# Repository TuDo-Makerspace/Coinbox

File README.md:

# Coinbox <!-- omit in toc -->

Our sacred Mario-themed coinbox!

https://github.com/user-attachments/assets/13c91ebd-0a8e-42fc-bb54-711a1d9b547c

## Table of Contents <!-- omit in toc -->

- [Building the Box](#building-the-box)
  - [Step 1. Cut the Wood](#step-1-cut-the-wood)
  - [Step 2. Glue the Pieces Together](#step-2-glue-the-pieces-together)
  - [Step 3. Secure the Bottom](#step-3-secure-the-bottom)
  - [Step 4. Lid slit](#step-4-lid-slit)
  - [Step 5. Hole for DC Jack](#step-5-hole-for-dc-jack)
  - [Step 6. Paint the Base Coat](#step-6-paint-the-base-coat)
  - [Step 7. Draw the Pixel Grid](#step-7-draw-the-pixel-grid)
  - [Step 8. Paint the Pixel Art](#step-8-paint-the-pixel-art)
  - [Step 9. Magnets for the Lid](#step-9-magnets-for-the-lid)
- [Electronics](#electronics)
  - [Components Required](#components-required)
  - [Wiring the Components](#wiring-the-components)
- [Software](#software)
  - [Overview](#overview)
  - [Configurable Parameters](#configurable-parameters)
  - [Sound Playback Implementation](#sound-playback-implementation)
- [Flashing the Arduino](#flashing-the-arduino)
- [Electronics Enclosure](#electronics-enclosure)
  - [Enclosure Components](#enclosure-components)
  - [Assembly Instructions](#assembly-instructions)
    - [1. Mounting the Perfboard](#1-mounting-the-perfboard)
    - [2. Attaching Speaker and Sensor](#2-attaching-speaker-and-sensor)
    - [3. Connecting Components](#3-connecting-components)
    - [4. Securing the Enclosure](#4-securing-the-enclosure)
    - [5. Sensor Calibration](#5-sensor-calibration)
    - [6. Screwing on the Lid](#6-screwing-on-the-lid)

## Building the Box

### Step 1. Cut the Wood

For the box, we cut 2 slightly larger pieces (dimensions: X x Y x Z) and 4 slightly smaller pieces (dimensions: X x Y x Z). The larger pieces make up the top and bottom, while the smaller pieces form the sides.

<div align="center">
  
</div>

### Step 2. Glue the Pieces Together

Once the pieces are cut, glue them together to form the box. Make sure the edges are flush and the corners are square.

<div align="center">
  
</div>

### Step 3. Secure the Bottom

Attach the bottom of the box using screws or nails for extra stability. Glue alone can work but might not be as durable.

<div align="center">
  
</div>

### Step 4. Lid slit

Cut a slit in the lid to allow coins to be inserted into the box. Make sure the slit is wide enough to accommodate different coin sizes.
We used a size of X x Y.

TODO: Add Image

### Step 5. Hole for DC Jack

Drill a hole into the bottom of any side of the box to make room for a DC jack. We didn't have a panel mount DC jack, so we used a PCB one and simply glued it into the hole. We also soldered a JST connector to the jack so that it can be easily connected to the electronics, while still allowing the other electronics to be removed from the box for maintenance.

### Step 6. Paint the Base Coat

Apply a white base layer of paint to the box. This will make the final colors more vibrant. Acrylic paint is recommended.

<div align="center">
  
</div>

### Step 7. Draw the Pixel Grid

Sketch a 16x16 pixel grid on the box. This will serve as a guide for your Super Mario-inspired design.

<div align="center">
  
</div>

### Step 8. Paint the Pixel Art

Fill in the grid with bright colors to create the iconic Mario Question Block design.

<div align="center">
  
</div>

### Step 9. Magnets for the Lid

Drill a hole into each corner of the box and lid. Insert and glue magnets into the holes. This allows the lid to remain in place, while still being easy to open.

<div align="center">
  
</div>

## Electronics

### Components Required

For the electronics setup, you'll need the following components:

- [Arduino Nano](https://www.amazon.de/s?k=Arduino+Nano&__mk_de_DE=%C3%85M%C3%85%C5%BD%C3%95%C3%91&crid=3MXT58JWGCI1J&sprefix=arduino+nano%2Caps%2C266&ref=nb_sb_noss_1)
- [PAM8403 Audio Amplifier Board](https://www.amazon.de/DollaTek-5V-Audioverst%C3%A4rker-Digitalendstufenmodul-Stereo-Verst%C3%A4rker-Potentiometer/dp/B07DJWGQVY?__mk_de_DE=%C3%85M%C3%85%C5%BD%C3%95%C3%91&crid=1J93G4RTHNOFI&dib=eyJ2IjoiMSJ9.VhFuJe_HzTWLwSzEMBKpXFbfVtzs2xYtEsEcFcNJW79MmodkhwESMPAF4hMxpNsp0-RtEiSU0jpFWjLN6wg4Uh0vlSXejNPPZRRUxNYW6l2bvtorope1h_9zDVZtlMFMt0HjKH_Bk_8RWcQRxPCO4W1f2i8Bn9ZUj9mRGoBzgtLDuuWy1e2-qZlDaqRN5sK5nutfB3Dzmlis4UT9MsrU4Z4mUlF12QH7MGjD_NL6tp0.1uOtyvjElgoe6sIg9TxoRxXoK5-NXYwmV4qZVtqTFH4&dib_tag=se&keywords=PAM8403&nsdOptOutParam=true&qid=1733056713&sprefix=pam8403%2Caps%2C105&sr=8-2)
- [KY-033 Line Tracking Sensor](https://www.amazon.de/KY-033-Anwendbar-Erkennung-Hindernissen-Infrarot-Detektionssensor/dp/B0D3XHR2VL?__mk_de_DE=%C3%85M%C3%85%C5%BD%C3%95%C3%91&crid=MDH7EVJABT7X&dib=eyJ2IjoiMSJ9.RlWEZOeTZ6sX26dyjT0VmGvXaeIfe0fNiByvESi-JRt_FZR3Czo7iebwAGvBumJAelrtNeD11kGk4plvt2SibF7ZavvEvt6HKnx9A1VgZRml4DGNf-TgQ_SI-_ZS7jZzyRd70TkvhrM8Ig6ntrBxQ1nZQlnfWuBosK6gG7Xac6ihUxQLUWqaLZ8wOClqj3F31IZYP-n7x6sgGrzlViW510Wuwf9rC21fS7sicuKGQy-2l57FHOTPyvg5kidcf0uDQc1LAN3Xo-Z77ALUQ3fuT8ywZoZEUQqflm4GeRQ55Sw.gUU66QJH7FSnTXfdb2mQlKu5cXOdB008n-60jFciu4c&dib_tag=se&keywords=KY-033+Line+Tracking+Sensor&nsdOptOutParam=true&qid=1733056743&sprefix=ky-033+line+tracking+sensor%2Caps%2C95&sr=8-2)
- [Speaker (8- or 4-ohm, rated for 3W or higher)](https://www.amazon.de/s?k=3w+speaker&__mk_de_DE=%C3%85M%C3%85%C5%BD%C3%95%C3%91&crid=1BIROBN0IAU2I&sprefix=3w+speake%2Caps%2C105&ref=nb_sb_noss_2)

### Wiring the Components

Connect the components as illustrated in the circuit diagram below:

> TODO: Add Circuit Diagram

For our project, we soldered the components onto a perfboard:

> Tip: We utilized JST connectors for connecting the speaker, sensor, and power supply to the perfboard. This allows for better maintainability.

## Software

> Firmware v3 now lives in the ESP-IDF project at the repo root (see `main/` and `README_IDF.md`). The notes below capture the earlier Arduino-based build for reference.

### Overview

The project's software can be found in the [`src/`](src/) directory. It performs the following actions:

1. Initialization:
   - Initializes GPIO's and serial communication.
   - Displays a playful ASCII art message in the serial monitor.

2. Sensor Monitoring:
   - Continuously monitors input from the KY-033 line tracking sensor.
   - Detects objects (e.g., coins) passing over the sensor by detecting a transition from LOW to HIGH on the sensor pin.

3. Sound Playback:
   Once a coin is detected:
   - Standard: Plays the classic Mario coin sound effect each time a coin is detected.
   - Special: On every *n-th* coin (configurable), it plays either a One-Up or Power-Up sound effect instead of the standard coin sound. Currently, the Power-Up sound is played on every 4th coin and the One-Up sound on every 10th coin.

### Configurable Parameters

At the top of the main file, you can adjust the following parameters:

- `POWER_UP`: Determines the number of coins required to play the Power-Up sound effect.
- `ONE_UP`: Determines the number of coins required to play the One-Up sound effect.
- `SENSOR_PIN`: Specifies the pin connected to the KY-033 sensor.
- `WAIT_AFTER_COIN`: Sets the waiting time between consecutive sound playbacks. This prevents spam if the coin is detected for a longer duration.

### Sound Playback Implementation

We utilize [Damellis's PCM Library](https://github.com/damellis/PCM) to handle audio playback. To play a sound, we can use the startPlayback() function, which takes an array of raw 8-bit audio values. The Mario audio samples are stored in the `sounds.h` file as byte arrays, however, due to copyright restrictions, `sounds.h` is not included in this repository. Makerspace Members can access the file on our file server. For others, refer to this [Tutorial](https://highlowtech.org/?p=1963) for instructions.

## Flashing the Arduino

To upload the software to your Arduino Nano, follow these steps:

1. Install PlatformIO:
   - Download and install [PlatformIO](https://platformio.org/) as an extension for your preferred IDE (e.g., VS Code).

2. Open the Project:
   - Launch PlatformIO and open this project by navigating to `File > Open Folder` and selecting the project's root directory.

3. Connect Your Arduino:
   - Use a USB cable to connect your Arduino Nano to your computer.

4. Upload the Firmware:
   - In PlatformIO, click the Upload button (usually represented by an arrow icon) to compile and flash the software to your Arduino.

## Electronics Enclosure

To securely house the electronics and ensure proper protection, we designed and 3D printed a custom enclosure tailored specifically to our components (i.e. our Speaker, Perfboard etc.). Provided that you likely have different components, you will need to come up with your own enclosure design. **This section mostly serves as a reference for members of our makerspace to repair or modify our coin box.**

### Enclosure Components

The enclosure consists of three main parts. Click on the links below to download the corresponding `.3mf` files:

- [Back Part](enclosure/Back.3mf): Holds the perfboard containing the Arduino Nano and the Audio Amplifier.
- [Front Part](enclosure/Front.3mf): Houses the speaker and the sensor.
- [Lid](enclosure/Lid.3mf): Covers the enclosure once the front and back parts are assembled.

### Assembly Instructions

#### 1. Mounting the Perfboard

Secure the perfboard onto the Back Part of the enclosure using M2 screws.

#### 2. Attaching Speaker and Sensor

Attach the speaker and KY-033 sensor to the Front Part of the enclosure using M3 screws and a nut.

> Note: Do not fully tighten the nut for the sensor yet, as you may need to adjust its position later.

#### 3. Connecting Components

Connect the sensor, speaker, and DC barrel jack to the perfboard.

#### 4. Securing the Enclosure

Screw the front and back parts together using M3 screws. Then insert the assembled electronics into the wooden box. This may require some force. Use two wooden screws from the bottom of the wooden box to secure the enclosure in place through the designated holes.

#### 5. Sensor Calibration

- Before attaching the lid, power up the electronics and calibrate the sensor sensitivity to detect coins.
- Place the box lid on top of the enclosure.
- Test the sensor by inserting small coins. If the sensor misses any coins, adjust its position by loosening the nut, repositioning the sensor, and then tightening the nut once satisfied.

#### 6. Screwing on the Lid

Once the sensor is properly positioned, secure the 3D printed lid onto the enclosure using three M3 screws and one M2 screw.

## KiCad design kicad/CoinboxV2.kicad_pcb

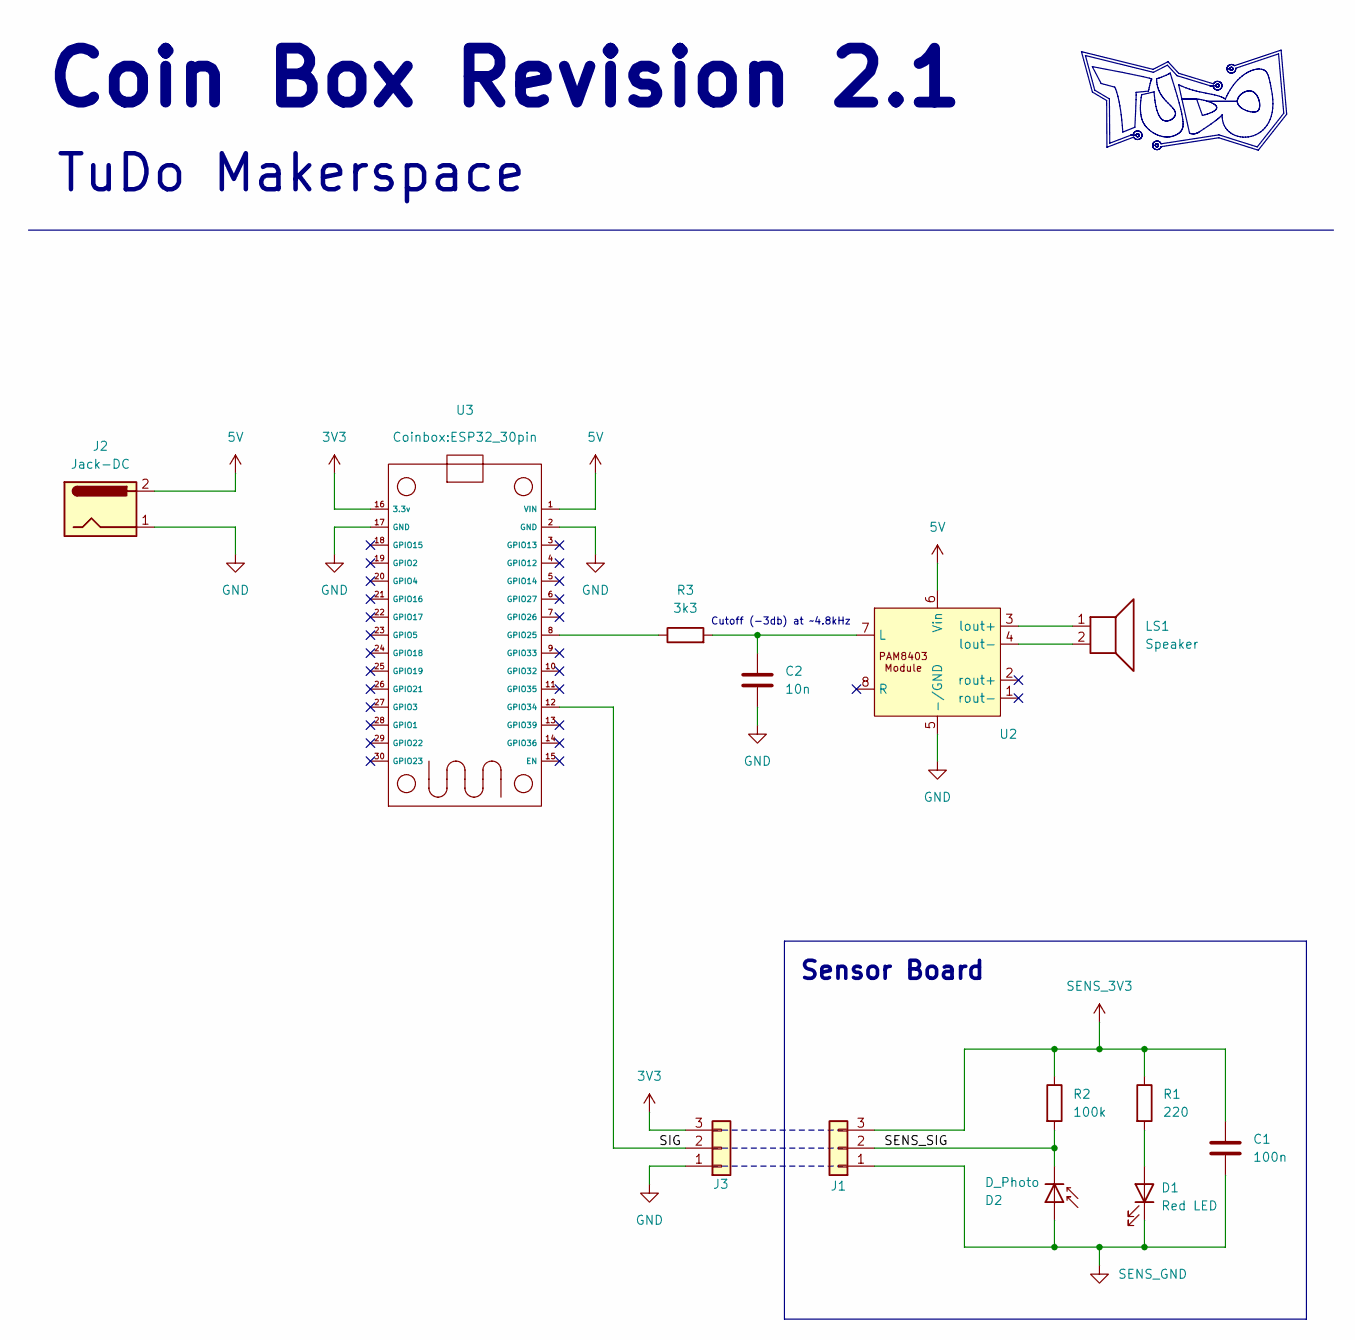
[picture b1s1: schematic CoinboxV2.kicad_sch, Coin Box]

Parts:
C1: 100n; C_1206_3216Metric_Pad1.33x1.80mm_HandSolder
C2: 10n; C_Disc_D6.0mm_W2.5mm_P5.00mm
D1: Red LED; LED_D5.0mm
D2: D_Photo; LED_D5.0mm
J1: Conn_01x03; SolderWire-0.1sqmm_1x03_P3.6mm_D0.4mm_OD1mm
J2: Jack-DC; JST_PH_B2B-PH-K_1x02_P2.00mm_Vertical
J3: Conn_01x03; JST_XH_B3B-XH-A_1x03_P2.50mm_Vertical
LS1: Speaker; JST_XH_B2B-XH-A_1x02_P2.50mm_Vertical
R1: 220; R_1206_3216Metric_Pad1.30x1.75mm_HandSolder
R2: 100k; R_1206_3216Metric_Pad1.30x1.75mm_HandSolder
R3: 3k3; R_Axial_DIN0207_L6.3mm_D2.5mm_P7.62mm_Horizontal
U2: PAM8403 Module
U3: ESP32_30pin

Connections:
3V3: J3.3, U3.16 (3.3v)
5V: J2.2, U2.6 (Vin), U3.1 (VIN)
/SENS_SIG: D2.1 (K), J1.2, R2.2
/SIG: J3.2, U3.12 (GPIO34)
GND: C2.2, J2.1, J3.1, U2.5 (-/GND), U3.2 (GND), U3.17 (GND)
unnamed: D1.2 (A), R1.2
unnamed: C2.1, R3.2, U2.7 (L)
unnamed: LS1.1, U2.3 (lout+)
unnamed: LS1.2, U2.4 (lout-)
unnamed: R3.1, U3.8 (GPIO25)
SENS_3V3: C1.1, J1.3, R1.1, R2.1
SENS_GND: C1.2, D1.1 (K), D2.2 (A), J1.1

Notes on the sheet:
Sensor Board
Cutoff (-3db) at ~4.8kHz
Coin Box Revision 2.1
TuDo Makerspace

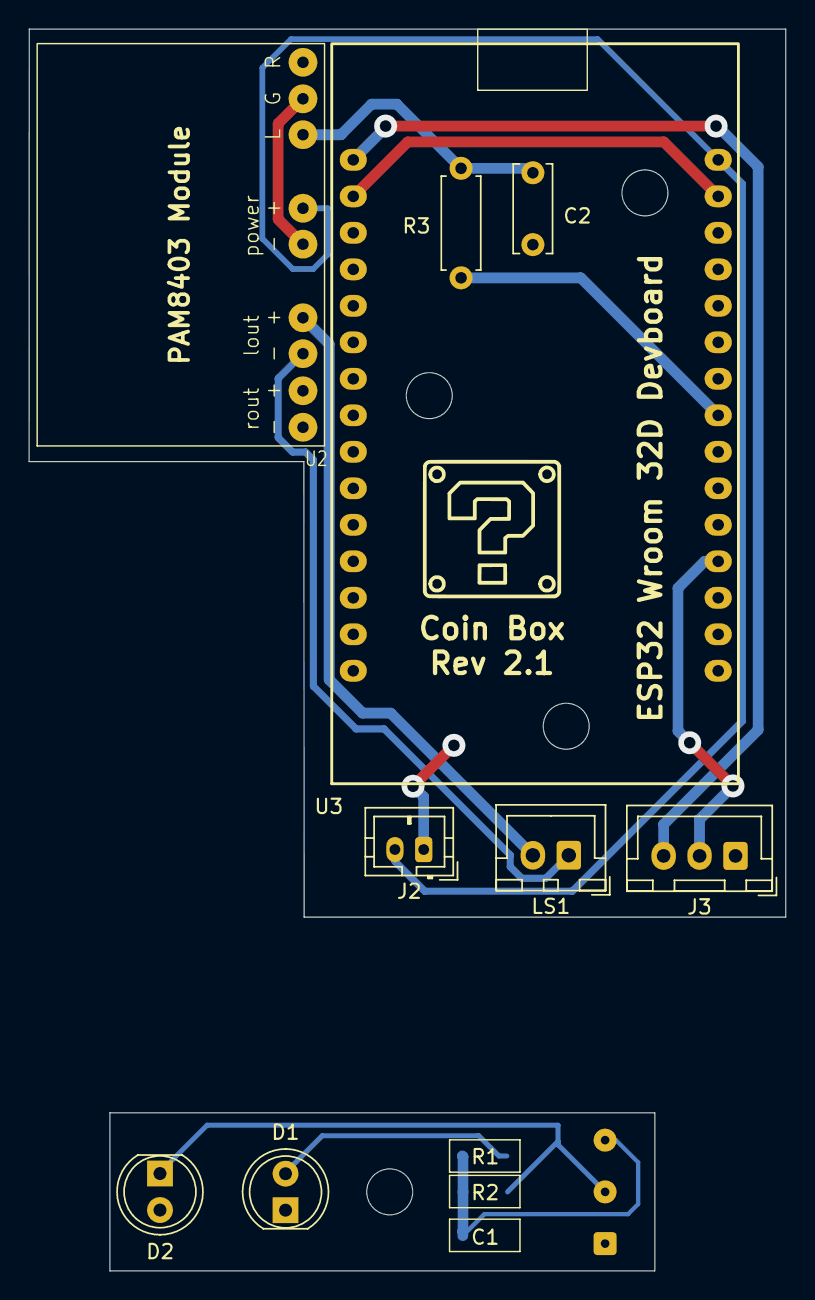
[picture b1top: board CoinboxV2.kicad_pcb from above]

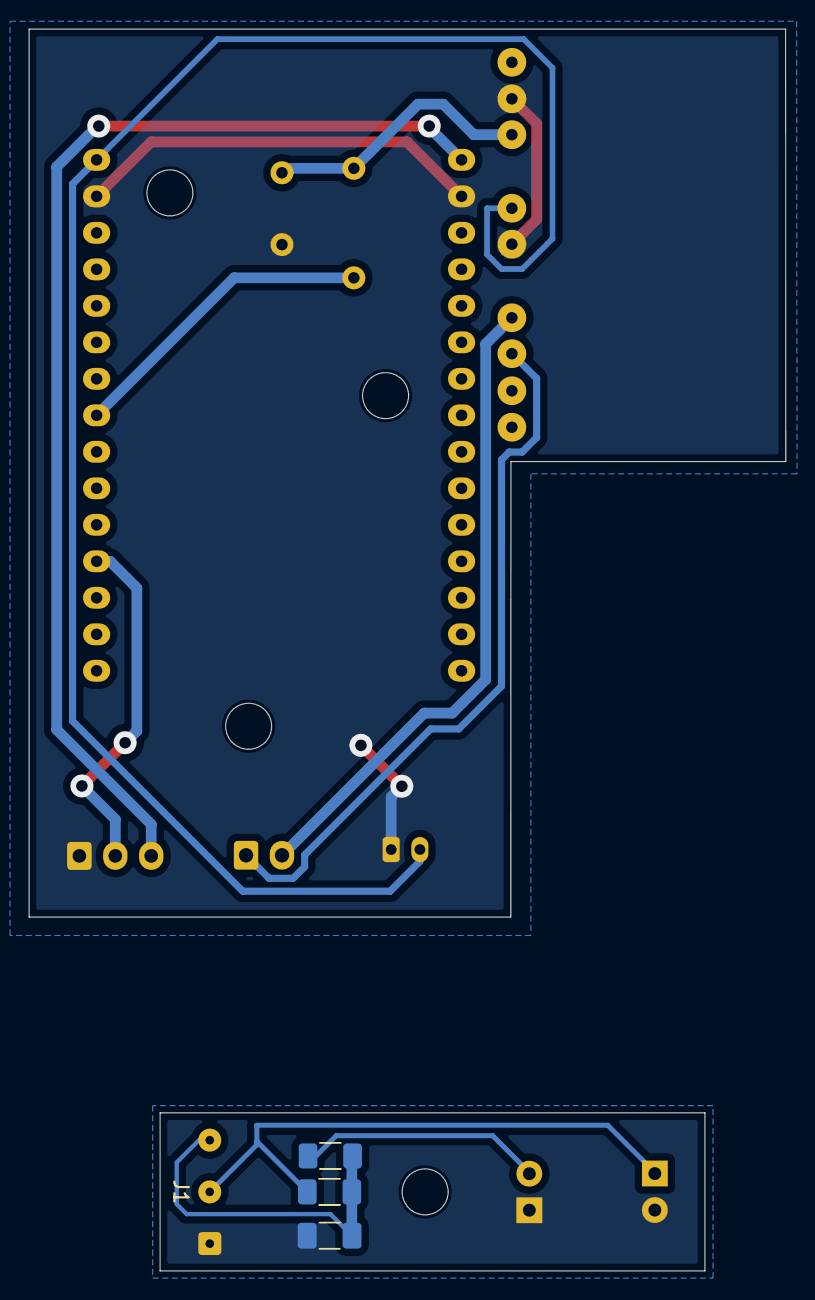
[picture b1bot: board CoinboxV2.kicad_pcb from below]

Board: 2 copper layers, 52.7 x 86.4 mm, 13 parts (4 on the bottom side), 12 nets.

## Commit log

2022-10-25 added source code for the awesome box
2024-11-26 Updated to work with new board
2024-11-26 Use analogRead for A6/A7 only
    From https://docs.arduino.cc/language-reference/en/functions/digital-io/digitalread/:
    The analog input pins can be used as digital pins, referred to as A0, A1, etc. The exception is the Arduino Nano, Arduino Pro Mini, and Arduino Mini’s A6 and A7 pins, which can only be used as analog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
2024-11-30 Docs
2024-11-30 README: Updated showcase
2024-11-30 README: Reduced size of perfboard image
2024-12-01 Github is not co-operating
2024-12-01 README: Update
2024-12-01 README: Minor changes
2024-12-01 README: Added links for components
2025-05-21 Use new sensor + Perform signal processing for better coin detection
2025-07-23 Initial commit of revision 2
2025-07-23 Add comments, format code, etc
2025-07-23 Added screenshot of new enclosure
2025-07-28 initial git
2025-07-28 Rough draft for app
2025-07-30 Improved lid detection + Updated GUI
2025-07-30 App: Added pyproject.toml
2025-07-30 App: Fixed search screen lag + Windows fixes
2025-07-30 Added timeout for config mode
2025-07-30 Disabled wifi reactivation
2025-07-30 App: Updated search screen note
2025-07-30 App: Fixed alignment on sample buttons
2025-07-30 App: Request restart on window close just to be sure
2025-07-30 App: Minor
2025-08-03 Uploading Samples Docs
2025-08-03 Docs: Update
2025-08-05 fixed some ota things
2025-08-05 Docs: Screen size fixes
2025-08-06 PCB Rev 2.1
2025-08-06 Docs: Add assembly instructions
2025-08-13 Docs: WIP
2025-08-13 App: Added checkboxes to toggle audio processing steps
2025-12-11 change max sample duration
2025-12-11 flash_ota.sh
2025-12-11 web server: rework endpoints + fix navbar
2025-12-11 add logger + log window in maintenance view
2025-12-11 update IO configuration in README.md for clarity on GPIO modes
2025-12-11 refine IO configuration table in README.md for clarity on GPIO modes
2025-12-12 work in progress
2025-12-12 webui: too many improvements
2025-12-12 Implement audio playback task and update GPIO handling for task management
2025-12-12 Initialize GPIO configuration and audio system in app_main
2025-12-12 Add GPIO and audio headers to main.c for initialization
2025-12-12 Refactor audio and GPIO header files to declare volume and ISR variables as extern
2025-12-12 rework file stuff
2025-12-12 file-server: add play button (not functional yet)
2025-12-13 repo: move project to repo root
2025-12-13 add boot-strapping to recover from bootloops
2025-12-13 add mdns component
2025-12-13 register mdns at config.local
2025-12-14 network: boot even if wifi connection fails
2025-12-15 maintenance: add audio test
2025-12-15 maintenance: audio_test: add volume slider
2025-12-15 maintenance: add sensor data
2025-12-15 bootstrap: serve in html files
2025-12-16 implement audio playback via esp-adf
2026-03-06 major refactor
    - Major rework and clean-up of existing firmware code.
    - Centralized all i2s related audio stuff to use esp-adf with a custom board def.
    - Added various amounts of front-end and back-end features (e.g. more recovery features, more front-end eye-candy, etc.)
    - Added QEMU support to emulate the firmware
    - Added integration tests (uses QEMU)
    - And much more...
2026-03-06 Settings: add reset button
2026-03-06 Settings: switched up the layout
2026-03-06 Boostrap: fix handover not working if auth enabled
2026-03-06 tests: add + move front-end tests to test_browser.py
2026-03-06 Front-end: move connection monitor to seperate js
2026-03-06 Audio: fix dangling pointer crash after repeated playback
2026-03-06 mdns: remove service where it actually makes sense
2026-03-06 mnds + network: add section comments
2026-03-06 Network: add option to disable AP once connected to wi-fi
2026-03-06 Network: disable power saving features
2026-03-06 Sounds: Add ro default sound
2026-03-06 Tests: Test if renaming to existing file is rejected
2026-03-06 Boot: Implement start-up sound
2026-03-06 Tests: Add tests for 0% volume and weights
2026-03-07 Security: Implement auth on recovery features w/ recovery code support
2026-03-07 Bootstrap: render as much as possible on client side
2026-03-07 Webserver: Ensure js deps are loaded bedfore they are required
2026-03-07 Add boot-aware reconnect handling for restarts and handoff
2026-03-07 Settings: Cut down on polling times
2026-03-07 Network: Fix poor concurrent client handling
2026-03-07 OTA: Add auth for OTA
2026-03-07 Tests: Make sure reset test is authenticated
2026-03-07 Tests: Add dockerized integration test runner to parallelize
2026-03-08 Tests: Always use smaller partition table for tests
2026-03-08 Audio: Fix regression in audio tests
2026-03-08 Settings: Implement lid open and closed volumes
2026-03-08 Sounds: Add warnings + Tweaked settings sliders
2026-03-08 Sounds: Skip sound playback if its volume is 0%
2026-03-08 CSS: Set min website width to 320px
2026-03-08 Docs: Clean up + Add HL components overview
2026-03-08 Audio: Fix test vol jumping when launching sweep
2026-03-08 Security: Move security API to seperate module
2026-03-09 Tests: Relax timeouts on browser tests
2026-03-09 Settings: Add debounce setting
2026-03-09 Config: Changed default AP credentials
2026-03-09 Boostrap: Increase conmon hand-off start delay to 6s
2026-03-09 Tets: Harden tests to work more reliably with docker containers
2026-03-10 Sounds: Fix special characters in file names
2026-03-10 QEMU: Mock heap usage during audio playback
2026-03-10 Tests: Add out-of-memory test during playback
2026-03-10 Settings: Reduce heap usage by sending a static html directly from flash
2026-03-10 Playback: Drop lid open/closed volumes
2026-03-10 Playback: Implement lid opening sound
2026-03-11 Tests: Harden
2026-03-16 Add MIT headers
2026-03-18 Settings: Minor visual tweaks
2026-03-18 Sounds: Add trim
2026-03-19 Sounds: Add lid closing sound
2026-03-19 Add vscode tasks
2026-05-19 Init: Fix bad init if wifi not available
2026-05-19 Create emergency hotspot if no wifi avail
